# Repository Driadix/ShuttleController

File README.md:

# ShuttleController

STM32 firmware for the shuttle racking system controller. This module runs the real machine: motion control, lifter control, safety checks, sensors, BMS integration, persistent configuration, direct display UART, and E22 radio communication with the handheld remote.

## Build
- Production build/upload is done only with Arduino IDE and the team-approved STM32 Arduino board/core settings.
- `platformio.ini` exists only for simple compile verification. PlatformIO is not the production build path and must not define project behavior.

Open `Cntrl_V2/Cntrl_V2.ino` in Arduino IDE to build or upload.

## Main Files
- `Cntrl_V2/Cntrl_V2.ino` - main controller sketch and state machine.
- `Cntrl_V2/ShuttleProtocol.h` - shared packed wire protocol used by controller, remote, and display.
- `Cntrl_V2/E22Radio.hpp` - header-only E22 radio helper for controller/remote links.
- `Cntrl_V2/TOF_Sense.*` - TOF sensor support.
- `Cntrl_V2/BmsDdA5*.hpp` - BMS integration.
- `Cntrl_V2/AlertManager.h` - fault/warning handling.

## Communication
- `SerialLora` connects to the E22 radio module for the remote.
- `SerialDisplay` connects directly to the display/Wi-Fi bridge.
- `SerialRS485`, CAN, GPIO sensors, and TOF are local controller interfaces.

Radio should stay mostly request-response: remote polling for heartbeat/status, sensors, stats, and config. Display UART can receive pushed telemetry/sensors/stats because it is wired.

## Reliability Notes
Target radio operation is up to 100 m in warehouse shuttle-racking conditions. Manual movement over radio must keep working with delayed packets: about 80 ms at 4k-class air data rate and up to about 150 ms in bad 2k-class scenarios.

Preserve ACK handling, command acceptance gates, error/channel checks, and the manual radio hold watchdog when changing motion or communication code.

## Validation
Documentation-only changes do not require a firmware compile. Firmware changes should be verified in Arduino IDE first, with PlatformIO only as an extra compile check. Hardware validation is required for motion, safety, radio, protocol, BMS, CAN, TOF, and display UART changes.

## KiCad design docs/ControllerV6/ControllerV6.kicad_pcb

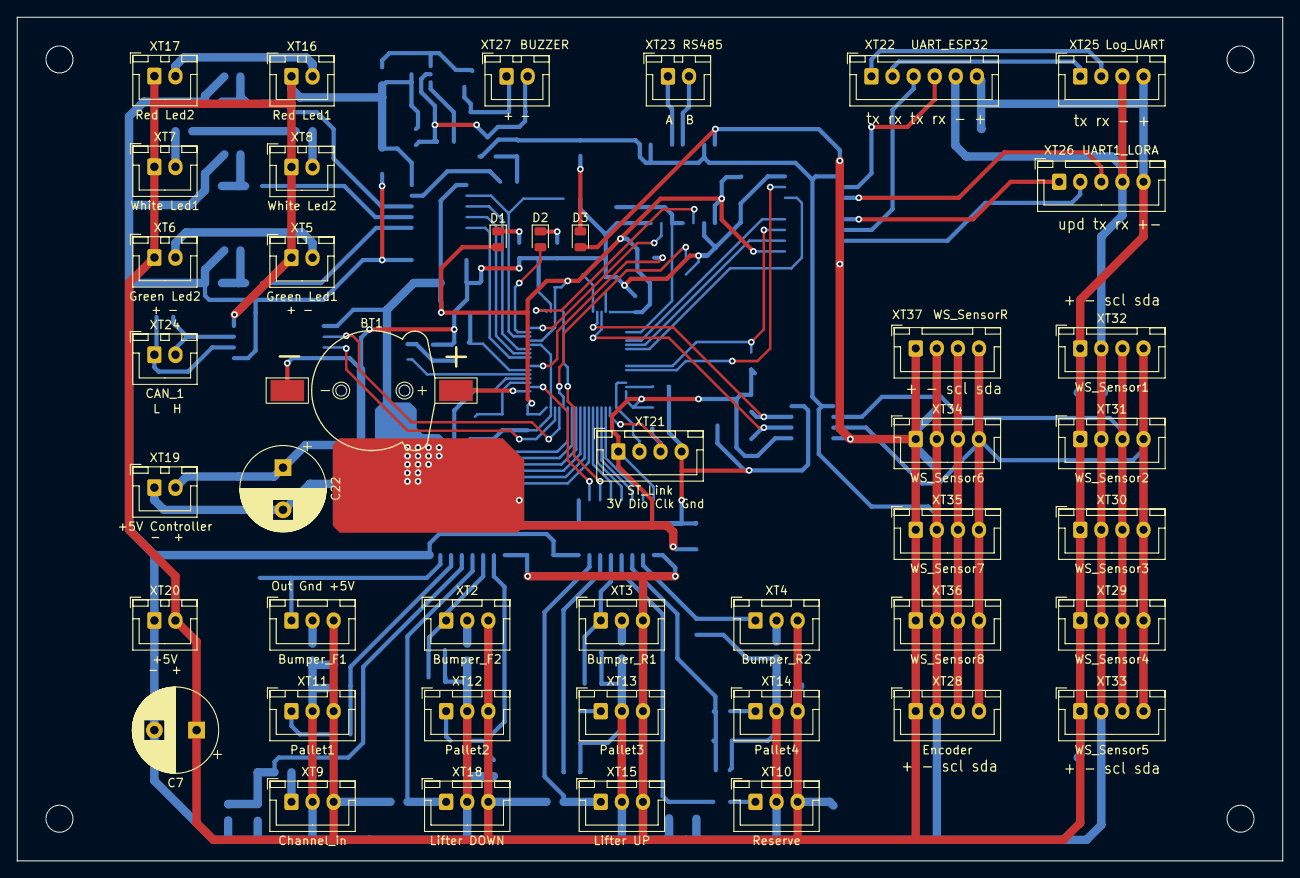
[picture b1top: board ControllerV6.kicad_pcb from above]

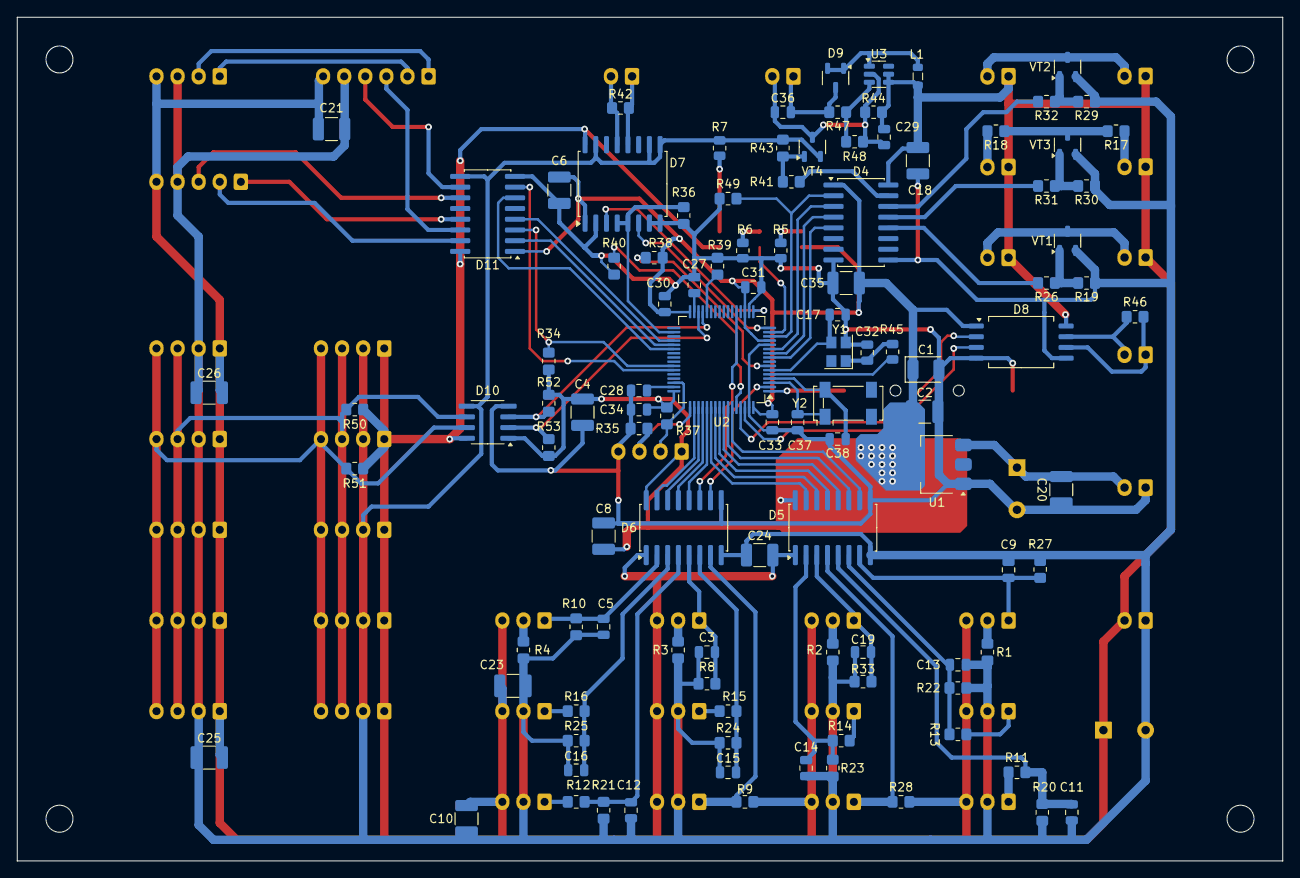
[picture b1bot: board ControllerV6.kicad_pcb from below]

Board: 2 copper layers, 150.0 x 100.0 mm, 150 parts (107 on the bottom side), 102 nets.

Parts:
BT1: +3V; BatteryHolder_RUICHI_856_CR1220
C1: 47u; CP_EIA-3528-21_Kemet-B
C2, C4, C6, C8, C10, C17, C18, C20, C21, C23, C24, C25, C26: 22u; C_1210_3225Metric_Pad1.33x2.70mm_HandSolder
C3, C5, C9, C11, C12, C13, C14, C15, C16, C19, C30, C31, C33, C34: 100n; C_0805_2012Metric
C7, C22: 100u; CP_Radial_D10.0mm_P5.00mm
C27, C28, C29, C36: 2.2u; C_0805_2012Metric
C32, C35: 18pF; C_0805_2012Metric
C37, C38: 12pF; C_0805_2012Metric
D1, D3: LED_VDD; LED_0805_2012Metric
D2: LED_USER; LED_0805_2012Metric
D4, D11: CA-IS3762; SOIC-16W_5.3x10.2mm_P1.27mm
D5, D6: CA-IS3760; SOIC-16W_5.3x10.2mm_P1.27mm
D7: CA-IS3082; SOIC-16W_7.5x10.3mm_P1.27mm
D8: CA-IS3050G; SOIC-8_7.5x5.85mm_P1.27mm
D9: BAT54CW; SOT-23-3
D10: CA-IS3020S; SOIC-8_3.9x4.9mm_P1.27mm
L1: 4.7U; L_0805_2012Metric
R1, R2, R3, R4, R17, R18: 200; R_0805_2012Metric_Pad1.20x1.40mm_HandSolder
R5, R6, R7: 1.2K; R_0805_2012Metric
R8, R10, R27, R33, R34, R44, R47: 20k; R_0805_2012Metric_Pad1.20x1.40mm_HandSolder
R9, R28, R35, R36, R37, R38, R39, R40, R49, R52, R53: 6.8k; R_0805_2012Metric_Pad1.20x1.40mm_HandSolder
R11, R12, R13, R14, R15, R16: 1k; R_0805_2012Metric_Pad1.20x1.40mm_HandSolder
R19, R29, R30, R43: 360; R_0805_2012Metric_Pad1.20x1.40mm_HandSolder
R20, R21, R22, R23, R24, R25, R50, R51: 3k; R_0805_2012Metric_Pad1.20x1.40mm_HandSolder
R26, R31, R32, R41: 1.2k; R_0805_2012Metric_Pad1.20x1.40mm_HandSolder
R42, R46: 120; R_0805_2012Metric_Pad1.20x1.40mm_HandSolder
R45: 360; R_0805_2012Metric
R48: 1.5k; R_0805_2012Metric_Pad1.20x1.40mm_HandSolder
U1: AMS1117-3.3; SOT-223-3_TabPin2
U2: STM32F405RGTx; LQFP-64_10x10mm_P0.5mm
U3: MT3608; SOT-23-6
VT1, VT2, VT3, VT4: BC817; SOT-23-3
XT1: Bumper_F1; JST_XH_B3B-XH-A_1x03_P2.50mm_Vertical
XT2: Bumper_F2; JST_XH_B3B-XH-A_1x03_P2.50mm_Vertical
XT3: Bumper_R1; JST_XH_B3B-XH-A_1x03_P2.50mm_Vertical
XT4: Bumper_R2; JST_XH_B3B-XH-A_1x03_P2.50mm_Vertical
XT5: Green Led1; JST_XH_B2B-XH-A_1x02_P2.50mm_Vertical
XT6: Green Led2; JST_XH_B2B-XH-A_1x02_P2.50mm_Vertical
XT7: White Led1; JST_XH_B2B-XH-A_1x02_P2.50mm_Vertical
XT8: White Led2; JST_XH_B2B-XH-A_1x02_P2.50mm_Vertical
XT9: Channel_in; JST_XH_B3B-XH-A_1x03_P2.50mm_Vertical
XT10: Reserve; JST_XH_B3B-XH-A_1x03_P2.50mm_Vertical
XT11: Pallet1; JST_XH_B3B-XH-A_1x03_P2.50mm_Vertical
XT12: Pallet2; JST_XH_B3B-XH-A_1x03_P2.50mm_Vertical
XT13: Pallet3; JST_XH_B3B-XH-A_1x03_P2.50mm_Vertical
XT14: Pallet4; JST_XH_B3B-XH-A_1x03_P2.50mm_Vertical
XT15: Lifter UP; JST_XH_B3B-XH-A_1x03_P2.50mm_Vertical
XT16: Red Led1; JST_XH_B2B-XH-A_1x02_P2.50mm_Vertical
XT17: Red Led2; JST_XH_B2B-XH-A_1x02_P2.50mm_Vertical
XT18: Lifter DOWN; JST_XH_B3B-XH-A_1x03_P2.50mm_Vertical
XT19: +5V Controller; JST_XH_B2B-XH-A_1x02_P2.50mm_Vertical
XT20: +5V; JST_XH_B2B-XH-A_1x02_P2.50mm_Vertical
XT21: ST_Link; JST_XH_B4B-XH-A_1x04_P2.50mm_Vertical
XT22: UART_ESP32; JST_XH_B6B-XH-A_1x06_P2.50mm_Vertical
XT23: RS485; JST_XH_B2B-XH-A_1x02_P2.50mm_Vertical
XT24: CAN_1; JST_XH_B2B-XH-A_1x02_P2.50mm_Vertical
XT25: Log_UART; JST_XH_B4B-XH-A_1x04_P2.50mm_Vertical
XT26: UART1_LORA; JST_XH_B5B-XH-A_1x05_P2.50mm_Vertical
XT27: BUZZER; JST_XH_B2B-XH-A_1x02_P2.50mm_Vertical
XT28: Encoder; JST_XH_B4B-XH-A_1x04_P2.50mm_Vertical
XT29: WS_Sensor4; JST_XH_B4B-XH-A_1x04_P2.50mm_Vertical
XT30: WS_Sensor3; JST_XH_B4B-XH-A_1x04_P2.50mm_Vertical
XT31: WS_Sensor2; JST_XH_B4B-XH-A_1x04_P2.50mm_Vertical
XT32: WS_Sensor1; JST_XH_B4B-XH-A_1x04_P2.50mm_Vertical
XT33: WS_Sensor5; JST_XH_B4B-XH-A_1x04_P2.50mm_Vertical
XT34: WS_Sensor6; JST_XH_B4B-XH-A_1x04_P2.50mm_Vertical
XT35: WS_Sensor7; JST_XH_B4B-XH-A_1x04_P2.50mm_Vertical
XT36: WS_Sensor8; JST_XH_B4B-XH-A_1x04_P2.50mm_Vertical
XT37: WS_SensorR; JST_XH_B4B-XH-A_1x04_P2.50mm_Vertical
Y1: 8MHz; Crystal_SMD_3225-4Pin_3.2x2.5mm
Y2: 32.7KHz; Crystal_SMD_Abracon_ABS25-4Pin_8.0x3.8mm

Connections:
3.3V_1: C1.1, C2.2, C4.2, C6.2, C8.2, C17.2, C30.2, C31.2, C33.2, C34.2, D1.2 (A), D4.1 (VDA), D5.16 (VDDB), D6.16 (VDDB), D7.1 (VDDA), D8.1 (Vcc1), D10.1 (VDDA), D11.1 (VDA), R34.2, R37.1, R38.1, R52.2, R53.2, U1.2 (VO), U2.13 (VDDA), U2.19 (VDD), U2.32 (VDD), U2.48 (VDD), U2.64 (VDD), XT21.1
5V: C7.1, C10.1, C18.1, C21.2, C23.2, C24.2, C25.2, C26.2, C29.2, D3.2 (A), D4.16 (VDDB), D5.1 (VDA), D6.1 (VDA), D7.16 (VDDB), D8.8 (Vcc2), D10.8 (VDDB), D11.16 (VDDB), L1.1, R9.1, R28.2, R44.2, R50.2, R51.2, U3.4 (EN), U3.5 (IN), XT1.3, XT2.3, XT3.3, XT4.3, XT5.1, XT6.1, XT7.1, XT8.1, XT9.3, XT10.3, XT11.3, XT12.3, XT13.3, XT14.3, XT15.3, XT16.1, XT17.1, XT18.3, XT20.2, XT22.6, XT25.4, XT26.5, XT28.1, XT29.1, XT30.1, XT31.1, XT32.1, XT33.1, XT34.1, XT35.1, XT36.1, XT37.1
5V_1: C20.2, C22.1, U1.3 (VI), XT19.2
Boot0_: R40.2, U2.60 (BOOT0)
Boot1: R39.2, U2.28 (PB2)
BumpF1_In: C9.2, D5.7 (VI6), R27.1, XT1.1
BumpF1_In_: D5.10 (VO6), U2.59 (PB7)
BumpF2_In: C19.2, D5.3 (VI2), R33.1, XT2.1
BumpF2_In_: D5.14 (VO2), U2.55 (PB3)
BumpR1_In: C3.2, D6.5 (VI4), R8.1, XT3.1
BumpR1_In_: D6.12 (VO4), U2.53 (PC12)
BumpR2_In: C5.2, D6.2 (VI1), R10.1, XT4.1
BumpR2_In_: D6.15 (VO1), U2.50 (PA15)
Buzzer: D4.15 (VO1), R41.1
Buzzer_: D4.2 (VI1), R49.2, U2.14 (PA0)
Can RX_: D8.2 (RXD), U2.61 (PB8)
Can TX_: D8.3 (TXD), U2.62 (PB9)
Can_H: D8.7 (CANH), R46.2, XT24.2
Can_L: D8.6 (CANL), R46.1, XT24.1
DI RS485: D7.6 (DI), U2.16 (PA2)
Esp32 RX: D11.10 (VI6), XT22.4
Esp32 RX_: D11.7 (VO6), U2.43 (PA10)
Esp32 TX: D11.14 (VO2), XT22.3
Esp32 TX_: D11.3 (VI2), R34.1, U2.42 (PA9)
GND: BT1.2 (-), C1.2, C2.1, C4.1, C6.1, C8.1, C17.1, C20.1, C22.2, C27.1, C28.1, C30.1, C31.1, C32.2, C33.1, C34.1, C35.2, C37.2, C38.2, D4.8 (GNDA), D5.9 (GNDB), D6.9 (GNDB), D7.2 (GNDA), D7.7 (GNDA), D7.8 (GNDA), D8.4 (GND1), D10.4 (GNDA), D11.8 (GNDA), R5.1, R6.1, R35.1, R36.1, R39.1, R40.1, R49.1, U1.1 (GND), U2.12 (VSSA), U2.18 (VSS), U2.63 (VSS), XT19.1, XT21.4, Y1.2, Y1.4
GNDREF: C3.1, C5.1, C7.2, C9.1, C10.2, C11.1, C12.1, C13.1, C14.1, C15.1, C16.1, C18.2, C19.1, C21.1, C23.1, C24.1, C25.1, C26.1, D4.9 (GNDB), D5.8 (GNDA), D6.8 (GNDA), D7.9 (GNDB), D7.10 (GNDB), D7.15 (GNDB), D8.5 (GND2), D10.5 (GNDB), D11.9 (GNDB), R1.1, R2.2, R3.1, R4.1, R7.1, R8.2, R10.2, R19.1, R20.2, R21.2, R22.2, R23.2, R24.2, R25.2, R27.2, R29.1, R30.1, R33.2, R43.2, VT1.2 (E), VT2.2 (E), VT3.2 (E), VT4.2 (E), XT9.2, XT10.2, XT11.2, XT12.2, XT13.2, XT14.2, XT15.2, XT18.2, XT20.1, XT22.5, XT25.3, XT26.4, XT28.2, XT29.2, XT30.2, XT31.2, XT32.2, XT33.2, XT34.2, XT35.2, XT36.2, XT37.2
Green Led: D4.12 (VO4), R26.2
Green Led_: D4.5 (VI4), U2.9 (PC1)
HSE1: R45.2, U2.5 (PH0)
HSE2: C35.1, U2.6 (PH1), Y1.3
In channel: C11.2, D5.5 (VI4), R11.2, R20.1
In channel_: D5.12 (VO4), U2.57 (PB5)
LSE1: C37.1, U2.3 (PC14), Y2.1
LSE2: C38.1, U2.4 (PC15), Y2.4
Led: D2.2 (A), U2.15 (PA1)
Lifter DOWN: D5.4 (VI3), R28.1, XT18.1
Lifter DOWN_: D5.13 (VO3), U2.56 (PB4)
Lifter UP: D6.7 (VI6), R9.2, XT15.1
Lifter UP_: D6.10 (VO6), U2.2 (PC13)
Lora_RX: D11.11 (VI5), XT26.3
Lora_RX_: D11.6 (VO5), U2.38 (PC7)
Lora_TX: D11.15 (VO1), XT26.2
Lora_TX_: D11.2 (VI1), U2.37 (PC6)
Lora_Upd: D11.13 (VO3), XT26.1
Lora_Upd_: D11.4 (VI3), U2.36 (PB15)
unnamed: C32.1, R45.1, Y1.1
unnamed: D1.1 (K), R5.2
unnamed: D2.1 (K), R6.2
unnamed: D3.1 (K), R7.2
unnamed: D7.12 (A), R42.2, XT23.1
unnamed: D7.13 (B), R42.1, XT23.2
unnamed: R47.1, R48.2, U3.3 (FB)
unnamed: C29.1, C36.1, R44.1, R48.1, U3.2 (GND), VT4.3 (C), XT27.2
unnamed: D9.1, D9.2, L1.2, U3.1 (SW)
unnamed: R19.2, R26.1, VT1.1 (B)
unnamed: VT1.3 (C), XT5.2, XT6.2
unnamed: R29.2, R32.1, VT2.1 (B)
unnamed: VT2.3 (C), XT16.2, XT17.2
unnamed: R30.2, R31.1, VT3.1 (B)
unnamed: R17.2, R18.1, VT3.3 (C)
unnamed: R41.2, R43.1, VT4.1 (B)
unnamed: R1.2, XT1.2
unnamed: R2.1, XT2.2
unnamed: R3.2, XT3.2
unnamed: R4.2, XT4.2
unnamed: R17.1, XT7.2
unnamed: R18.2, XT8.2
unnamed: R11.1, XT9.1
unnamed: R12.1, XT10.1
unnamed: R13.1, XT11.1
unnamed: R14.1, XT12.1
unnamed: R15.1, XT13.1
unnamed: R16.2, XT14.1
unnamed: XT22.1, XT25.2
unnamed: XT22.2, XT25.1
unnamed: C36.2, D9.3, R47.2, XT27.1
Pallet1: C13.2, D5.6 (VI5), R13.2, R22.1
Pallet1_: D5.11 (VO5), U2.58 (PB6)
Pallet2: C14.2, D5.2 (VI1), R14.2, R23.1
Pallet2_: D5.15 (VO1), U2.54 (PD2)
Pallet3: C15.2, D6.6 (VI5), R15.2, R24.1
Pallet3_: D6.11 (VO5), U2.21 (PA5)
Pallet4: C16.2, D6.3 (VI2), R16.1, R25.1
Pallet4_: D6.14 (VO2), U2.51 (PC10)
RE RS485: D7.4 (RE), D7.5 (DE), R36.2, U2.34 (PB13)
RO RS485: D7.3 (RO), U2.17 (PA3)
Red Led: D4.14 (VO2), R32.2
Red Led_: D4.3 (VI2), U2.11 (PC3)
Reserve: C12.2, D6.4 (VI3), R12.2, R21.1
Reserve_: D6.13 (VO3), U2.52 (PC11)
Reset_: R38.2, U2.7 (NRST)
SCL: D10.6 (SCLB), R50.1, XT28.3, XT29.3, XT30.3, XT31.3, XT32.3, XT33.3, XT34.3, XT35.3, XT36.3, XT37.3
SCL_: D10.3 (SCLA), R52.1, U2.29 (PB10)
SDA: D10.7 (SDAB), R51.1, XT28.4, XT29.4, XT30.4, XT31.4, XT32.4, XT33.4, XT34.4, XT35.4, XT36.4, XT37.4
SDA_: D10.2 (SDAA), R53.1, U2.30 (PB11)
SWCLK: R35.2, U2.49 (PA14), XT21.3
SWDIO: R37.2, U2.46 (PA13), XT21.2
VCAP_1: C27.2, U2.31 (VCAP_1)
VCAP_2: C28.2, U2.47 (VCAP_2)
Vbat: BT1.1 (+), U2.1 (VBAT)
White Led: D4.13 (VO3), R31.2
White Led_: D4.4 (VI3), U2.10 (PC2)

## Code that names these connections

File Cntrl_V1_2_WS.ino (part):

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
#pragma region Пины и дефайны...

#define DL_UP PC13       // Пин датчика положения лифтера в поднятом состоянии
#define DL_DOWN PB4      // Пин датчика положения лифтера в опущенном состоянии
#define DATCHIK_F1 PA5   // Пин датчика 1 обнаружения паллета вперед
#define DATCHIK_F2 PC4   // Пин датчика 2 обнаружения паллета вперед
#define DATCHIK_R1 PB6   // Пин датчика 1 обнаружения паллета назад
#define DATCHIK_R2 PD2   // Пин датчика 2 обнаружения паллета назад
#define GREEN_LED PC1    // Пин зеленого светодиода
#define BOARD_LED PA1    // Пин светодиода на плате
#define RED_LED PC3      // Пин красного светодиода ошибки
#define WHITE_LED PC2    // Пин белого светодиода работы
#define ZOOMER PA0       // Зумер
#define LORA PB15        // Пин включения радиомодуля
#define RS485 PB13       // Пин передачи шины RS485
#define BUMPER_F1 PB7    // Пин бампера вперед
#define BUMPER_F2 PB3    // Пин бампера вперед
#define BUMPER_R1 PA6    // Пин бампера назад
#define BUMPER_R2 PC5    // Пин бампера назад
#define CHANNEL PB5      // Пин датчика канала

#define FLASH_SECTOR_SIZE 4 * 1024  // 16 kb
#define EEPROM_PAGE_SIZE 512
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bool manualControlFromRadio = false;
bool pendingDisplayManualModeBypass = false;

HardwareSerial Serial1(PA10, PA9);                    // Порт для экранцика LilyGo 
HardwareSerial Serial2(PA3, PA2);                     // Порт под RS485 для BMS батареи 
HardwareSerial Serial3(PC7, PC6);                     // Порт Lora

STM32_CAN Can1(CAN1, ALT, RX_SIZE_256, TX_SIZE_256);  // CAN шина на пинах PB8 PB9
static CAN_message_t CAN_TX_msg;                      // Пакет данных CAN на передачу
static CAN_message_t CAN_RX_msg;                      // Пакет данных CAN на прием

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  CAN_TX_msg.flags.extended = 1;
  CAN_RX_msg.flags.extended = 1;

  Wire.setSDA(PB11);
  Wire.setSCL(PB10);
  Wire.begin();
  Wire.setClock(400000);

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
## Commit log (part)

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2025-02-27 init: add current shuttle contoller code
2025-02-27 feat: delete unused sd card logging logic
2025-04-04 refactor: styling
2025-04-04 feat: add commands processing from SRC
2026-02-18 Refactor Shuttle Protocol to robust binary format
    - Introduced ShuttleProtocol.h defining TLV structure, MsgIDs, and Packet types.
    - Implemented sendPacket and parseSerial1 (FSM) in Cntrl_V1_2_WS.ino.
    - Replaced Serial1.print logging with sendLog.
    - Implemented sendTelemetry and sendSensors.
    - Replaced blocking Serial1 reading with non-blocking FSM.
2026-02-18 Address PR Feedback: Cleanup Logs and Add Missing Commands
    - Cleaned up redundant logging in Cntrl_V1_2_WS.ino.
    - Implemented missing critical commands:
    - CMD_FIRMWARE_UPDATE (200) -> jumpToBootloader
    - CMD_SYSTEM_RESET (201) -> HAL_NVIC_SystemReset
    - CMD_SET_DATETIME (202) -> rtc.setTime/setDate
    - Expanded handleConfig to support shuttleNum, minBattCharge, waitTime, mprOffset, chnlOffset, fifoLifo, inverse, evacuate.
2026-02-19 refactor: delete copy
2026-02-19 feat: update logging system and comms protocol
2026-02-19 Refactor shuttle communication to binary protocol with CRC16 and robust parsing
2026-02-19 feat: update more logs to new protocol
2026-02-19 feat: delete unused comments, adjust remaining logging, add old lods to separate file for reference
2026-02-20 feat: add shuttle number for telemetry packet
2026-02-20 feat: adjust shuttle protocol
2026-02-20 Refactor protocol handling for concurrency safety and EEPROM efficiency
    - Isolated `sendLog` buffer: Replaced global `txBuffer` with a local `logBuffer` in `sendLog` to prevent race conditions with telemetry packets.
    - Updated `processPacket`:
    - Implemented `MSG_CONFIG_GET` handler to return current configuration parameters.
    - Added `CMD_SET_DATETIME` (202) handler with bit-packing logic for date/time sync.
    - Removed blocking `saveEEPROMData` call from `MSG_CONFIG_SET` to prevent flash wear and blocking behavior; configuration save now requires explicit `CMD_SAVE_EEPROM`.
    - Verified that `CMD_SAVE_EEPROM` (13) is correctly propagated to `run_Cmd` for execution.
2026-02-20 Fix CRC endianness and logging logic in STM32 controller
2026-02-20 Optimize shuttle logging: rate-limiting, state-change detection, and log level adjustments
2026-02-20 Implement persistent statistics tracking with wear leveling
    - Added tracking for load, unload, lift up/down, and total distance in EEPROM.
    - Implemented EEPROM wear leveling by splitting pages into Data (0-3) and Stat (4-7) partitions.
    - Added migration logic to move legacy data to the new partition scheme.
    - Implemented buffering (statsDirty flag) and safe save logic (on idle or distance threshold).
    - Fixed EEPROM transaction safety to prevent data loss on power failure during save.
    - Injected event hooks into shuttle logic functions.
2026-02-20 Implement Robust Memory Architecture: Backup SRAM Stats & Flash Configs
2026-02-24 feat: add backup sram for stats, adjust eeprom config load
2026-02-24 merge: adjust merge
2026-02-24 feat: adjust stats for protocol, add additional safe checks
2026-02-24 feat: deliver shuttle protocol with parser
2026-02-24 feat: update shuttle protocol shipping defines, crc, parser
2026-02-24 refactor: adjust namings
2026-02-27 feat: update shuttle protocol to v2
2026-02-27 feat: adjust protocol sizes, add command types
2026-02-27 feat: adjust comments
2026-02-27 Refactor Cntrl_V1_2_WS.ino to align with ShuttleProtocol V2
    - Route high-bandwidth telemetry to Serial1 (Display)
    - Swap parser associations for correct UART handling
    - Implement Protocol V2 sync bytes and scaled integer types
    - Replace legacy string-based commands with binary packet handlers
    - Secure sendLog with bounds checking and CRC
2026-02-27 fix: delete trash symb, adjust protocol sync var
2026-02-27 feat: add safety for 0x00 commands
2026-02-27 Refactor Cntrl_V1_2_WS.ino to fix packet swallowing and map protocol enums
    - Introduce `NO_NEW_CMD` (0xFF) to distinguish background packets (Telemetry, Sensors, etc.) from state-changing commands (Stop = 0x00).
    - Implement `mapCommandToLegacyStatus` adapter to translate `ShuttleProtocol.h` Enums to legacy magic numbers used in `run_Cmd`.
    - Update `processPacket` to return `NO_NEW_CMD` for non-command packets and use the mapper for commands.
    - Update `get_Cmd` to intercept mapped system commands (Firmware Update = 253, Reset = 254).
    - Fixes the issue where Heartbeat/Sensor packets (returning 0) were misinterpreted as STOP commands.
2026-03-02 feat: adjust some comments
2026-03-02 feat: adjust lora config
2026-03-02 refactor: change communication layer status codes to use ShuttleProtocol enums
2026-03-02 feat: add Provisioning State Default ID
2026-03-02 feat: replace telemetry getting, parsing serial and comms with unified system yield approach
2026-03-02 feat: add override command helper, adjust ack and busy states of shuttle
2026-03-02 feat: adjust loop
2026-03-02 feat: adjust main logic with yield and new state machine
2026-03-02 Refactor serial packet parsing, fix FSM trap, and prevent buffer saturation
2026-03-03 feat: add safety check for cmd config serial
2026-03-03 feat: add abort loop thing, adjust logic
2026-03-03 feat: get rid of trash files
2026-03-03 refactor(cntrl): rename SystemYield to IO_Update and move to top of loop
    - Renamed `SystemYield()` to `IO_Update()` everywhere in the codebase to conceptually reflect its purpose as a pure Layer 1 state synchronization step, not a time-yielding mechanism.
    - Removed redundant manual calls to `IO_Update()` from `if (millis() - count > X)` blocks inside `CoreOpMode::IDLE` and `CoreOpMode::MANUAL` loop cases. The `IO_Update()` function is already position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
    - The `IO_Update()` and its underlying `pollSerial()` functions remain strictly non-blocking. This allows the newly cleaned `loop()` to spin at its maxim
2026-03-03 Refactor lifter code to use non-blocking LifterManager class.
    Extracted blocking motor ramping and waiting delays from lifter_Up
    and lifter_Down functions into a non-blocking LifterManager class
    with a tick() state machine. The old functions are now synchronous
    wrappers around the state machine.
2026-03-03 Refactor `motor_Stop` to use non-blocking `MotorBrake` state machine
    - Implemented `MotorBrake` class containing `startBrake()` and `tick()` to decouple motor stopping sequence from blocking `delay()` calls.
    - `tick()` manages decreasing motor speed in a non-blocking loop driven by `millis()`.
    - Replaced the global `motor_Stop` with a non-blocking wrapper using `MotorBrake` and checking `IO_Update` on every iteration, freeing up the CPU for handling network packets during emergency stops o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
    - Ensures identical motor math output and identical 100ms LED blinking delays.
2026-03-04 Refactor `motor_Speed` to a non-blocking `MotorSpeedController` class
    - Extracted blocking motor control logic into `MotorSpeedController` class.
    - Replaced global `oldSpeed` with `motorSpeedController.currentSpeed`.
    - Moved stepping delays to non-blocking `tick()` function called via `IO_Update()`.
    - Implemented `forceSpeed(0)` on all crash and abort conditions to prevent ghost movement.
    - Improved CAN messaging payload bounds checks inside the class.
2026-03-04 Fix asynchronous speed ramping, correct LifterManager timing, and eliminate CAN bus read starvation
    - Added `clear_CAN_Buffer(uint32_t timeoutMs)` to replace bare CAN reads with bounded timeouts to prevent super-loop freezes.
    - Replaced `while (Can1.read(CAN_RX_msg));` loops across `MotorBrake` and `motor_Force_Stop` with the new timeout helper.
    - Modified `motor_Speed()` to implement a cooperative yielding block (`while (motorSpeedController.isRamping)`), correctly yielding and checking for aborts while awaiting the target physical speed.
    - Aligned `LifterManager` timeout tracking by shifting `stateStartTime = millis();` capture to strictly measure the mechanical lifting/lowering phase, pre
2026-03-04 feat: adjust serial writes/reads
2026-03-04 feat: add full config commands, adjust process logic
2026-03-04 feat: add eeprom save when error / check for motors off
2026-03-04 feat: add correct sizes for parser (tx/rx buf), add log asser
2026-03-04 refactor: adjust protocol
2026-03-05 feat: adjust manual control
2026-03-05 feat: adjust manual mode for 5s
2026-03-05 feat: adjust shuttleprotocol ack and shuttlestate
2026-03-05 feat: adjust compile time ack to be enum
2026-03-05 feat: adjusted shuttle state hanlding logic
2026-03-05 feat: adjust shuttle protocol signature
2026-03-05 feat: replace error code array with bitwise O(1) operations
2026-03-05 feat: adjust errors handling for sensors
2026-03-05 feat: get rid of reportData
2026-03-05 fix: adjust rx timeout
2026-03-05 fix: adjust port write not ot check
2026-03-05 Improve manual link handling and add shuttle link diagnostics
2026-03-05 Add structured shuttle timing diagnostics for link analysis
2026-03-06 refactor: adjust build artifacts
2026-03-06 feat: make connection logs restricted by define variable
2026-03-06 fix: adjust compilation errors
2026-03-10 feat: make usage of e32 header only library
2026-03-10 refactor: adjust comments
2026-03-10 feat: adjust to new hardware
2026-03-10 fix: adjust log size
2026-03-11 feat: adjust stm32 ota update logic and conditionals
2026-03-11 feat: add enhanced battery calculating
2026-03-11 feat: move bms read into dedicated library
2026-03-11 refactor: delete compatability old wrapper for battery reading
2026-03-11 feat: make basic channel 400, add reconfigure shuttle address
2026-03-11 refactor: rename main file
2026-03-12 feat: adjust battery limit protection handling
2026-03-12 feat: add reliable manual movement
2026-03-12 feat: adjust manual with one-tap
2026-03-12 feat: adjust manual timings
2026-03-12 feat: adjust manual move to tap (move cmd) + hold (just move untill got stop)
2026-03-13 feat: adjust manual control displaying
2026-03-13 feat: add additional pallete checks for sensors observability
2026-03-14 feat: добавить обработку дополнительных бамперов
2026-03-14 fix: adjust problem when sensors were dying for no reason
2026-03-14 fix: adjust warn timings for battery
2026-03-14 feat: add warnings
2026-03-14 feat: use faults from protocol
2026-03-14 feat: make usage of alert manager for errors / warnings
2026-03-17 feat: change radio settings
2026-03-17 feat: add reset in error / out of channel
2026-03-17 logs: add additional log for crash
2026-03-17 feat: adjust sensors auto recover to only self heal after error reset
2026-03-18 Add telemetry piggyback ACKs for radio commands
2026-03-18 Fix telemetry ACK state preview for radio commands
2026-03-18 deploy: move code to arduino / platformio shared architecture
2026-03-18 feat: add correct forward declarations, adjust platformio config
2026-03-19 fix: adjust distance check in channel
2026-03-19 format: adjust project with clang format
2026-03-19 feat: add cppcheck
2026-03-19 format: clang format
2026-03-19 feat: add attributes for file ends
2026-03-19 feat: adjust dependencies
2026-03-19 feat: look through clang format adjustments
2026-05-26 Remove E32Radio.hpp header file, eliminating all related definitions, structures, and functions for E32 radio configuration and communication.
2026-05-27 refactor: update E22 radio configuration to use structured initialization
2026-05-27 feat: enhance TOF sensor diagnostics and command handling
2026-05-27 feat: add logging for E22 radio configuration and diagnostics
2026-05-27 feat: update E22 radio configuration to use 240-byte subpacket size
2026-05-28 feat: update pin assignments for E22 radio module
2026-05-28 feat: disable LBT for E22 radio configuration
2026-05-29 feat: add link health diagnostics and packet handling for E22 radio configuration
2026-05-29 feat: enhance logging framework with dynamic log size and improved frame handling
2026-05-29 feat: implement bootloader reset functionality and SRAM access management
2026-05-29 feat: reduce bootloader entry grace period from 60ms to 15ms
2026-05-29 Enhance E22Radio diagnostics and update ShuttleProtocol version
    - Added EnsureDiagnostics struct to E22Radio for improved diagnostic tracking.
    - Updated EnsureResult to include diagnostics information.
    - Modified various functions in E22Radio to utilize diagnostics, including baud rate tracking and error counting.
    - Changed ShuttleProtocol version from 2 to 3 and added ResetReasonFlags enum for reset reasons.
    - Updated StatsPacket to include detailed reset counts and last reset flags.
    - Improved I2C communication in TOF_Sense with error handling and return values for read operations.
